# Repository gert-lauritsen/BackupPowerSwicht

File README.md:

En simpel og pålidelig strømforsynings-switch baseret på **LTC4359 ideal diode controller**. Enheden sørger automatisk for fejlfri overgang mellem primær strøm og backup-strømkilde, når hovedstrømmen forsvinder.

Perfekt til udstyr, der kræver kontinuerlig drift – f.eks. routere, overvågningskameraer eller netværksudstyr.

## Egenskaber

- **Automatisk failover** mellem hoved- og backup-strømforsyning
- **LTC4359-baseret**: effektiv og tabsfri styring af strømretningen
- **Ingen mikrokontroller eller software**
- **Indgangsspænding (Vin):** 4–80 V DC
- **Maks. udgangsstrøm:** 8,5 A (begrænset af stik og printbaner)
- **Passiv og vedligeholdelsesfri**

## Indhold

- `schematic/BackupPowerSwitch.pdf` – [Skematisk diagram](https://github.com/gert-lauritsen/BackupPowerSwicht/blob/main/BatteryBackup.pdf)

- `README.md` – Denne dokumentation

## Funktion

- To separate strømindgange: én til hovedforsyning og én til backup.
- LTC4359 styrer en MOSFET, som fungerer som en ideel diode med lavt spændingsfald.
- Ved spændingsudfald på hovedforsyningen, skifter systemet automatisk og øjeblikkeligt til backup.
- Når hovedforsyningen vender tilbage, overtager den igen automatisk.

## Anvendelsesområder

- UPS-løsninger til små enheder
- Netværksudstyr og routere
- IoT-installationer
- Kamera- og alarmsystemer

## Bemærkninger og begrænsninger

- Sørg for tilstrækkelig køling ved kontinuerlig belastning over 3 A
- Udgangen er ikke galvanisk adskilt – kun egnet til DC-spændinger
- LTC4359 prioriterer automatisk den højeste indgangsspænding – ikke egnet til aktiv paralleldrift

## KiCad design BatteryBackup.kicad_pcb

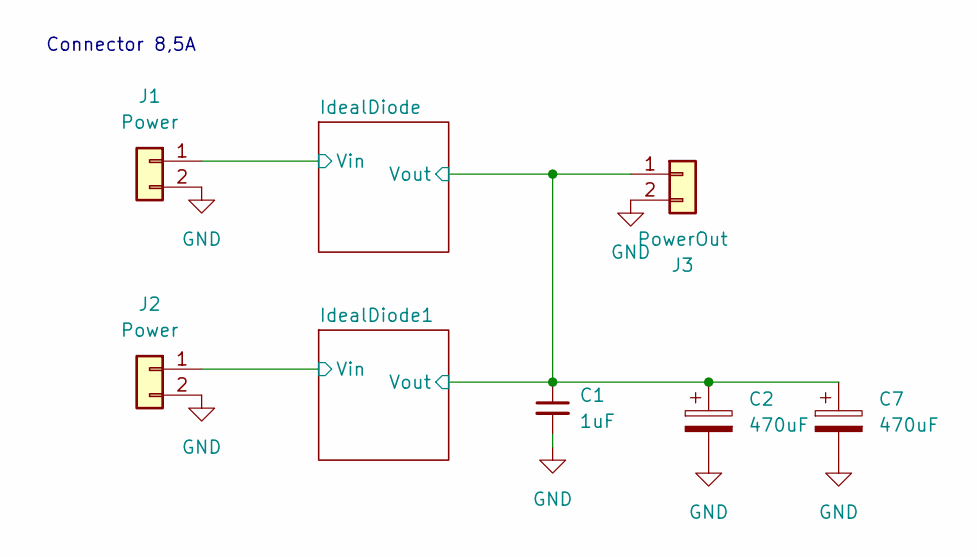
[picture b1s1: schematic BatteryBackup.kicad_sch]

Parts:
C1: 1uF; C_0805_2012Metric
C2, C7: 470uF; CP_Radial_D12.5mm_P5.00mm
J1, J2: Power; Molex_Micro-Fit_3.0_43650-0200_1x02_P3.00mm_Horizontal
J3: PowerOut; Molex_Micro-Fit_3.0_43650-0200_1x02_P3.00mm_Horizontal

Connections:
/IdealDiode1/Vin: J2.1; also elsewhere on the board
/IdealDiode/Vin: J1.1; also elsewhere on the board
/IdealDiode/Vout: C1.1, C2.1, C7.1, J3.1; also elsewhere on the board
GND: C1.2, C2.2, C7.2, J1.2, J2.2, J3.2; also elsewhere on the board

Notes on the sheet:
Connector 8,5A

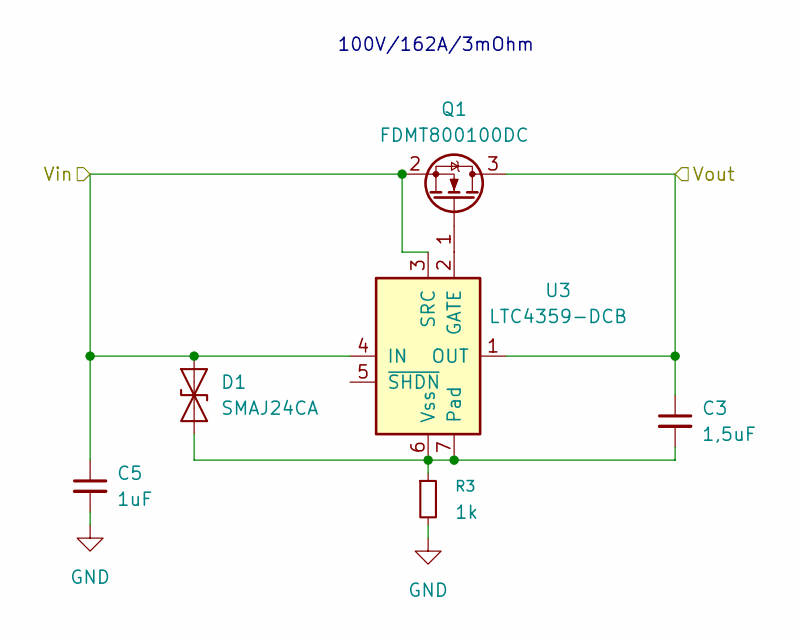
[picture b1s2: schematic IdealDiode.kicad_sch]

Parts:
C3: 1,5uF; C_0603_1608Metric
C5: 1uF; C_0805_2012Metric
D1: SMAJ24CA; D_SMA
Q1: FDMT800100DC; PQFN_8x8
R3: 1k; R_0603_1608Metric
U3: LTC4359-DCB; DFN-6-1EP_3x2mm_P0.5mm_EP1.65x1.35mm

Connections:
/IdealDiode/Vin: C5.1, D1.2 (A2), Q1.2 (S), U3.3 (SRC), U3.4 (IN); also elsewhere on the board
/IdealDiode/Vout: C3.1, Q1.3 (D), U3.1 (OUT); also elsewhere on the board
GND: C5.2, R3.2; also elsewhere on the board
unnamed: C3.2, D1.1 (A1), R3.1, U3.6 (Vss), U3.7 (Pad)
unnamed: Q1.1 (G), U3.2 (GATE)

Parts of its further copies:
C4: 1,5uF; C_0603_1608Metric
C6: 1uF; C_0805_2012Metric
D2: SMAJ24CA; D_SMA
Q2: FDMT800100DC; PQFN_8x8
R4: 1k; R_0603_1608Metric
U4: LTC4359-DCB; DFN-6-1EP_3x2mm_P0.5mm_EP1.65x1.35mm

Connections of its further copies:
/IdealDiode1/Vin: C6.1, D2.2 (A2), Q2.2 (S), U4.3 (SRC), U4.4 (IN); also elsewhere on the board
/IdealDiode/Vout: C4.1, Q2.3 (D), U4.1 (OUT); also elsewhere on the board
GND: C6.2, R4.2; also elsewhere on the board
unnamed: C4.2, D2.1 (A1), R4.1, U4.6 (Vss), U4.7 (Pad)
unnamed: Q2.1 (G), U4.2 (GATE)

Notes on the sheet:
100V/162A/3mOhm

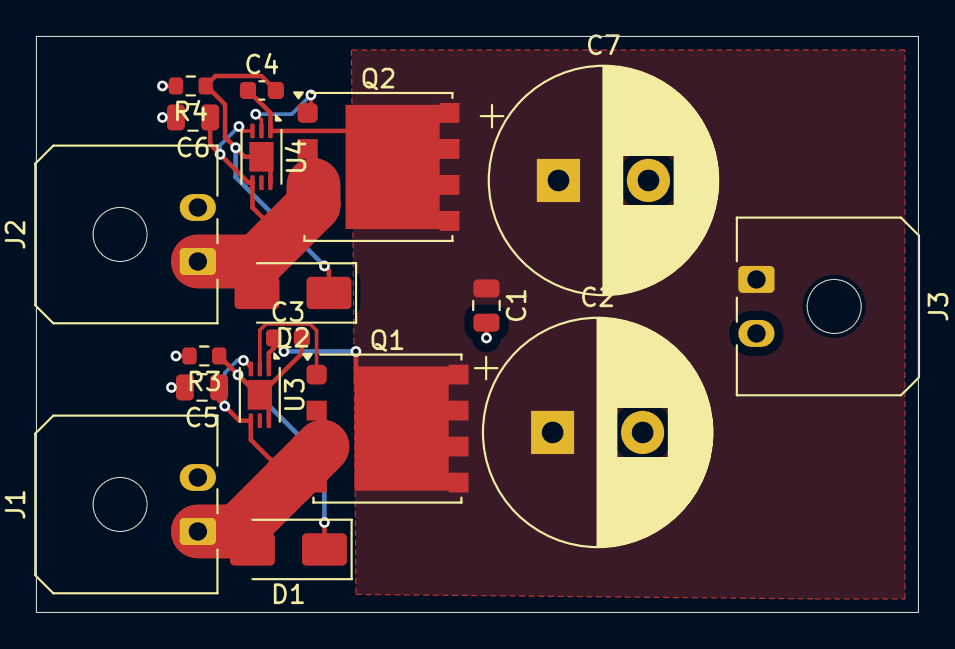
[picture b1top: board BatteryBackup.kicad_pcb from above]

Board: 2 copper layers, 49.0 x 32.0 mm, 18 parts (0 on the bottom side), 8 nets.

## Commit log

2025-07-01 pictures
2025-07-01 routet
2025-07-02 cooling
2025-07-03 skiftet til LTC4359
2025-07-03 fejlretning
2025-07-03 readme
